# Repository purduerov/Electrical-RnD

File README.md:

# Electrical-RnD

To create a new project:
1. Before you begin work, pull recent updates from the repo with:
	
	`git switch master`
	Or if you're old fashioned `git checkout master`.

	Then: `git pull`

2. Create a new branch for your part with (replace NEW_BRANCH_NAME with your own _new_ branch name):
	Make the branch name something descriptive like (Pi-Shield-Parts or Molex-nanofit)
  
	`git checkout -b NEW_BRANCH_NAME`
  
3. Create a folder for your project
	This helps keep the repo clean, please do it
	Give the folder the same name as the branch (Not required but it makes things simpler)
	`mkdir FOLDERNAME`
	`cd FOLDERNAME`

4. Work on your project
	Keep all of your files inside the project folder
	Download the datasheet for any part you use and save it in the project folder

4. Getting rid of eagle's backup files:

	`git clean -n -X`  To see what files would be removed  
	`git clean -f -X`  To remove said files

5. Add your changes with:

	`git add .`

6. Commit your changes (this saves them) with (replace your message with an explanation of what was added):

	`git commit -m "YOUR MESSAGE"`
	ex: `git commit -m "Made the 4 pin molex 371/372 series miniclamp connector (part XXXX) for the backplane board."`

7. Push your changes to the remote repo with (use the same name as before):

	`git push`.
	If the branch was just created, do `git push -u origin NEW_BRANCH_NAME`
	
8. Open a pull request on [GitHub](https://github.com/purduerov/Electrical-RnD/pulls) to merge your branch into master.

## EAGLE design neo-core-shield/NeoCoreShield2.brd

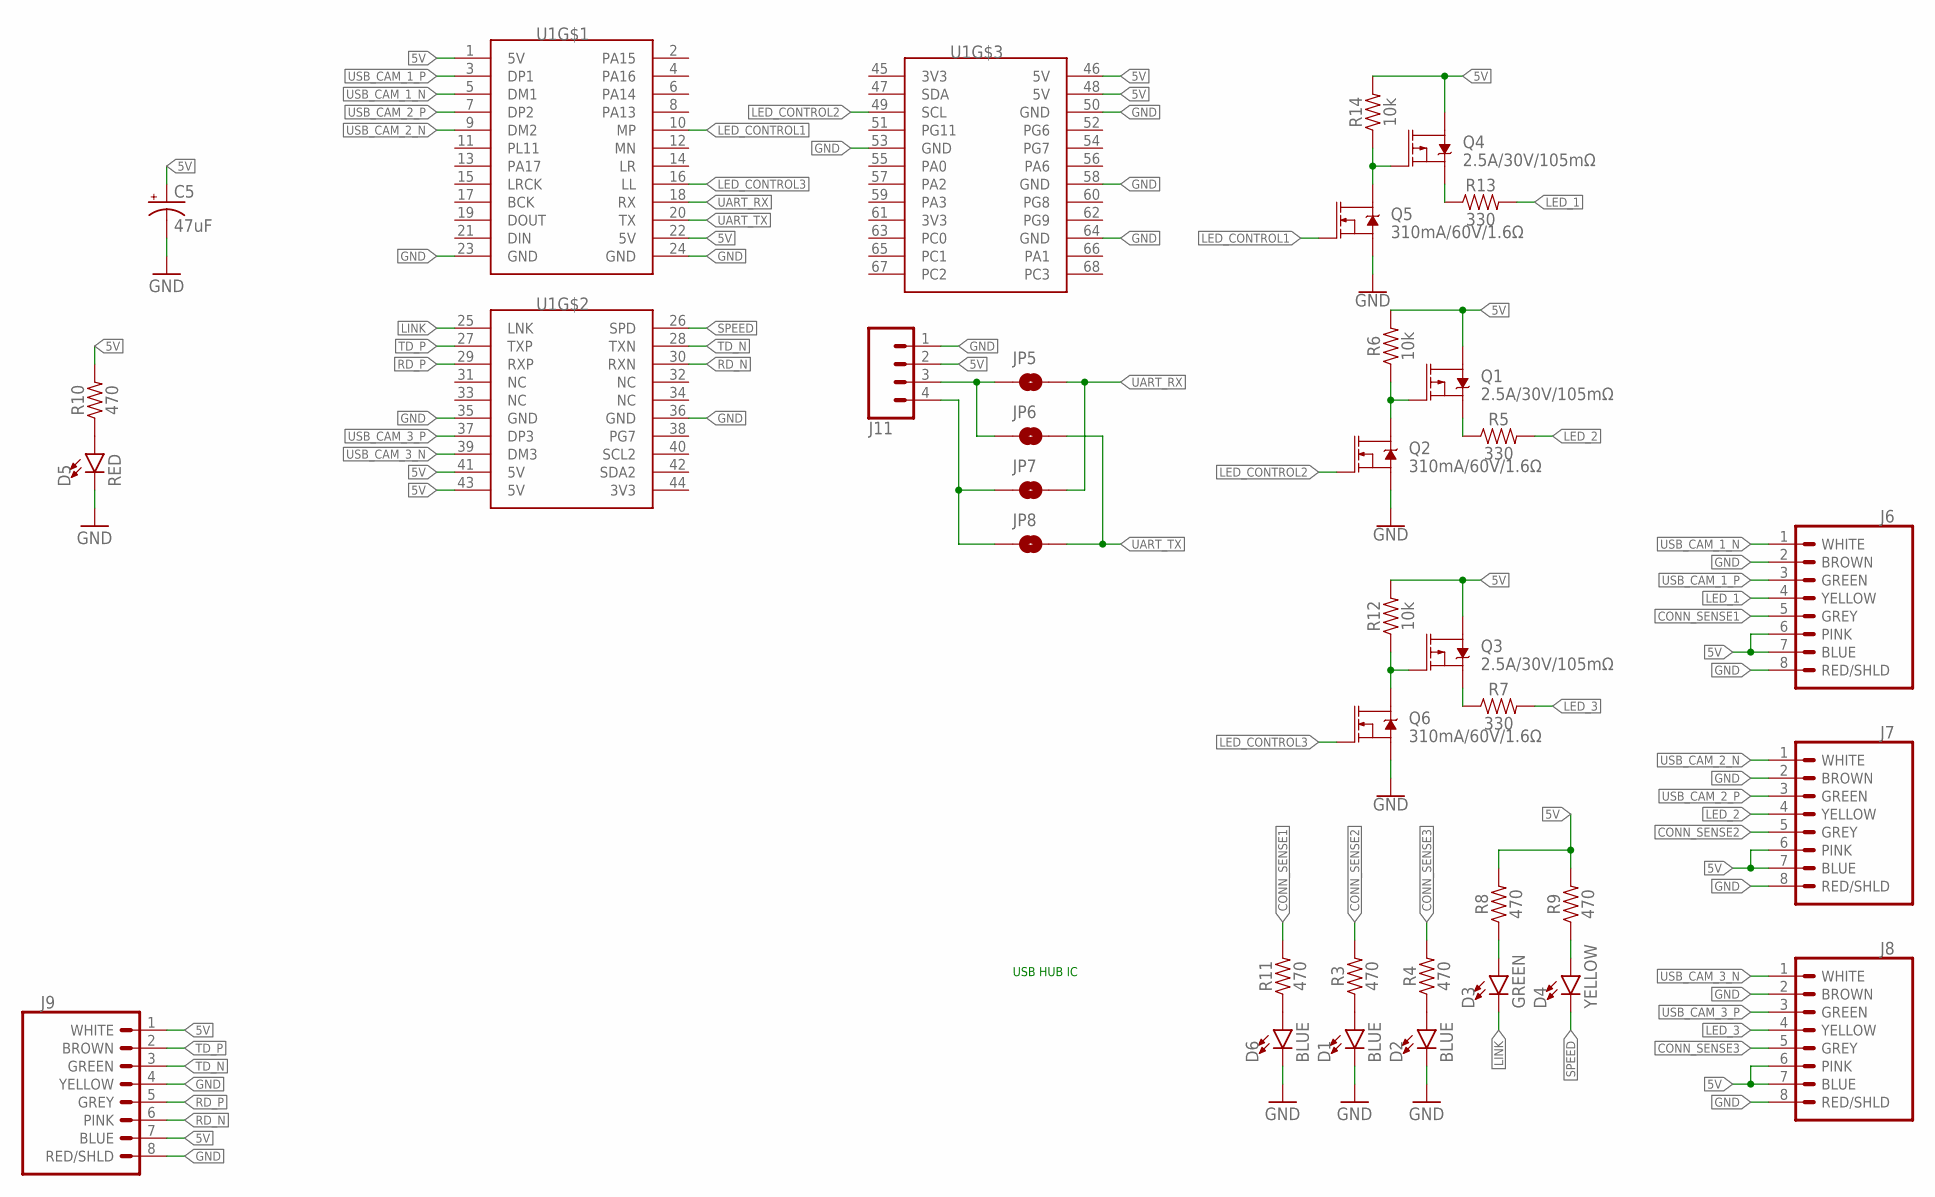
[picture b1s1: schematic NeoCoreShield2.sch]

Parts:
C5: 47uF; PANASONIC_D
D1, D2, D6: BLUE; 0805
D3: GREEN; 0805
D4: YELLOW; 0805
D5: RED; 0805
J6, J7, J8, J9: BINDER_M12_PAR_8_DIP
J11: CONN_04; 1X04
JP5, JP6, JP7, JP8: JUMPER-SMT_2_NO_SILK; SMT-JUMPER_2_NO_SILK
Q1, Q3, Q4: 2.5A/30V/105mΩ; SOT23-3
Q2, Q5, Q6: 310mA/60V/1.6Ω; SOT323
R3, R4, R8, R9, R10, R11: 470; 0603
R5, R7, R13: 330; 0805
R6, R12, R14: 10k; 0603
U1: NANO_PI_NEO_CORE

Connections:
5V: C5.+, J6.6 (PINK), J6.7 (BLUE), J7.6 (PINK), J7.7 (BLUE), J8.6 (PINK), J8.7 (BLUE), J9.1 (WHITE), J9.7 (BLUE), J11.2, Q1.3 (D), Q3.3 (D), Q4.3 (D), R6.2, R8.2, R9.2, R10.2, R12.2, R14.2, U1.1 (5V), U1.22 (5V), U1.41 (5V), U1.43 (5V), U1.46 (5V), U1.48 (5V)
CONN_SENSE1: J6.5 (GREY), R11.2
CONN_SENSE2: J7.5 (GREY), R3.2
CONN_SENSE3: J8.5 (GREY), R4.2
GND: C5.-, D1.C, D2.C, D5.C, D6.C, J6.2 (BROWN), J6.8 (RED/SHLD), J7.2 (BROWN), J7.8 (RED/SHLD), J8.2 (BROWN), J8.8 (RED/SHLD), J9.4 (YELLOW), J9.8 (RED/SHLD), J11.1, Q2.2 (S), Q5.2 (S), Q6.2 (S), U1.23 (GND), U1.24 (GND), U1.35 (GND), U1.36 (GND), U1.50 (GND), U1.53 (GND), U1.58 (GND), U1.64 (GND)
LED_1: J6.4 (YELLOW), R13.2
LED_2: J7.4 (YELLOW), R5.2
LED_3: J8.4 (YELLOW), R7.2
LED_CONTROL1: Q5.1 (G), U1.10 (MP)
LED_CONTROL2: Q2.1 (G), U1.49 (SCL)
LED_CONTROL3: Q6.1 (G), U1.16 (LL)
LINK: D3.C, U1.25 (LNK)
LINK_MID: D3.A, R8.1
unnamed: D1.A, R3.1
unnamed: D2.A, R4.1
unnamed: D6.A, R11.1
unnamed: Q3.2 (S), R7.1
unnamed: Q3.1 (G), Q6.3 (D), R12.1
unnamed: D5.A, R10.1
unnamed: Q1.2 (S), R5.1
unnamed: Q1.1 (G), Q2.3 (D), R6.1
unnamed: Q4.2 (S), R13.1
unnamed: Q4.1 (G), Q5.3 (D), R14.1
RD_N: J9.6 (PINK), U1.30 (RXN)
RD_P: J9.5 (GREY), U1.29 (RXP)
SPEED: D4.C, U1.26 (SPD)
SPEED_MID: D4.A, R9.1
TD_N: J9.3 (GREEN), U1.28 (TXN)
TD_P: J9.2 (BROWN), U1.27 (TXP)
UART_RX: JP5.2, JP7.2, U1.18 (RX)
UART_RX_TX: J11.3, JP5.1, JP6.1
UART_TX: JP6.2, JP8.2, U1.20 (TX)
UART_TX_RX: J11.4, JP7.1, JP8.1
USB_CAM_1_N: J6.1 (WHITE), U1.5 (DM1)
USB_CAM_1_P: J6.3 (GREEN), U1.3 (DP1)
USB_CAM_2_N: J7.1 (WHITE), U1.9 (DM2)
USB_CAM_2_P: J7.3 (GREEN), U1.7 (DP2)
USB_CAM_3_N: J8.1 (WHITE), U1.39 (DM3)
USB_CAM_3_P: J8.3 (GREEN), U1.37 (DP3)

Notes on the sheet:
USB HUB IC

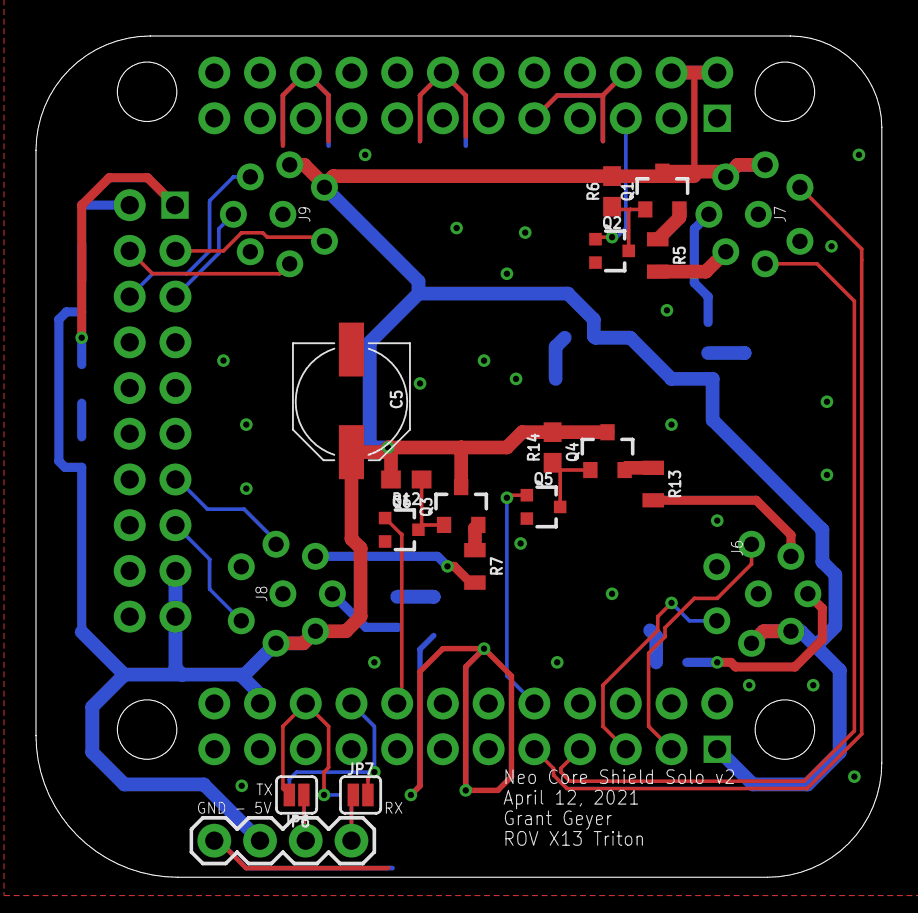
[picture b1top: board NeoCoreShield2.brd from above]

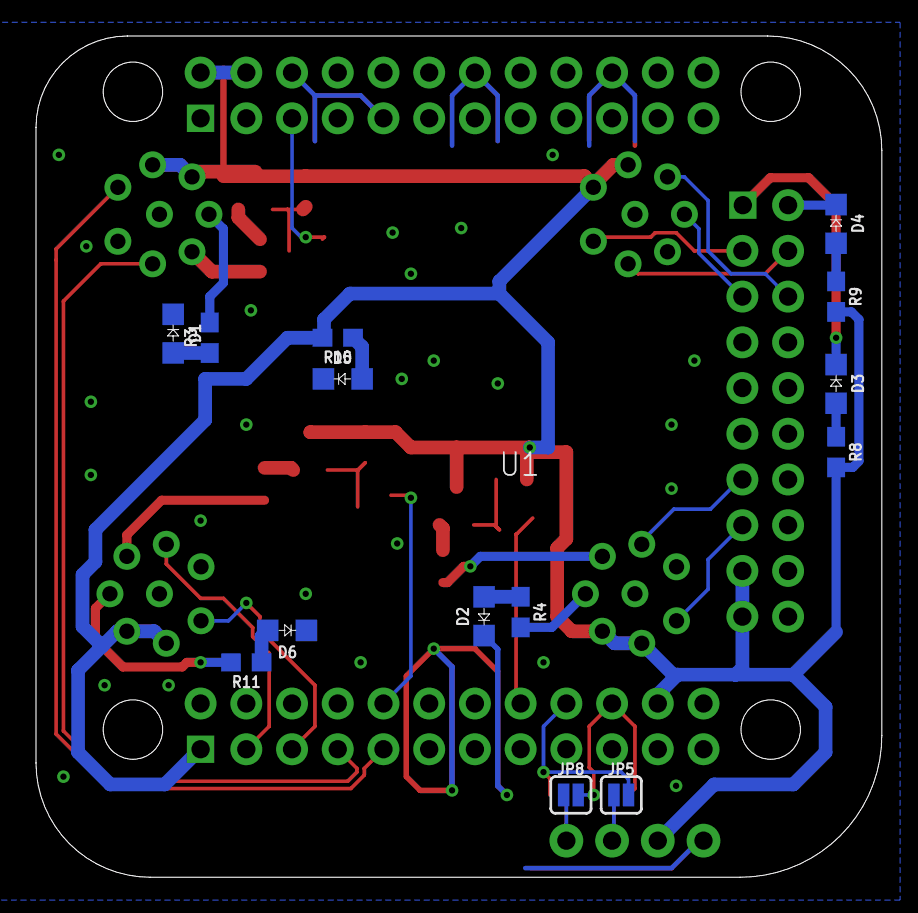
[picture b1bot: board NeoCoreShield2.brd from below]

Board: 2 copper layers, 47.0 x 46.7 mm, 35 parts (15 on the bottom side), 39 nets.

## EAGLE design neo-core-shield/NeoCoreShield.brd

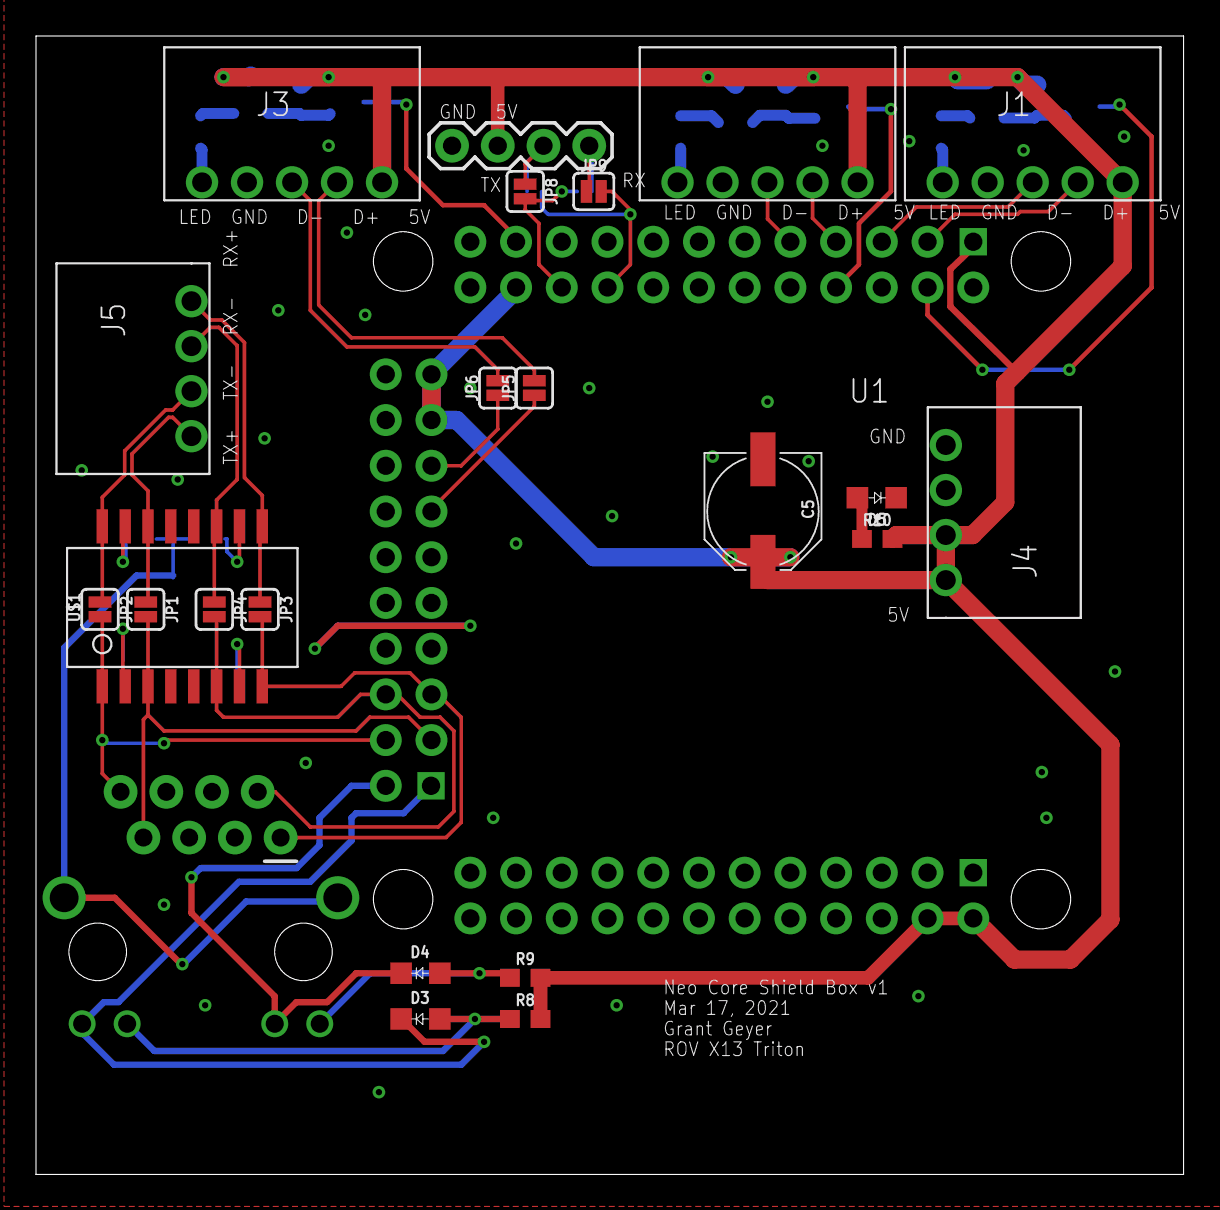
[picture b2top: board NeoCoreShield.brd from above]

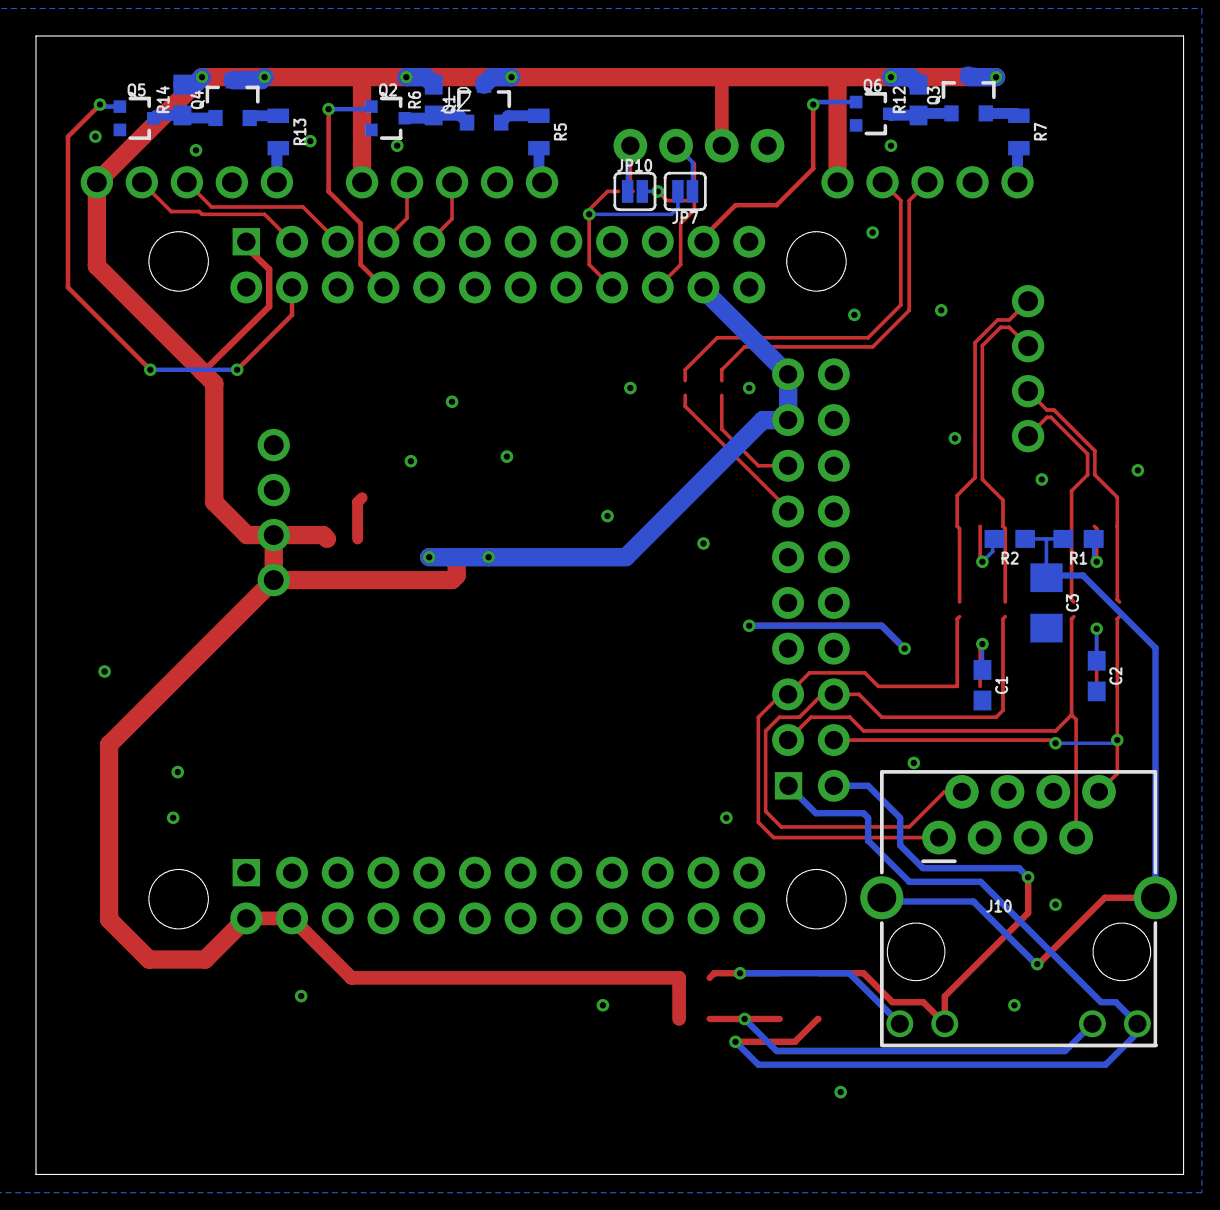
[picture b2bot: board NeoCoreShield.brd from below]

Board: 2 copper layers, 63.8 x 63.2 mm, 43 parts (20 on the bottom side), 44 nets.

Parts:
C1, C2: 0.1uF; 0603
C3: 1.0nF; 1206
C5: 47uF; PANASONIC_D
D3: GREEN; 0805
D4: YELLOW; 0805
D5: RED; 0805
J1, J2, J3: PXC-PTSM-05-RA
J4, J5: PXC-PTSM-04-RA-1778641
J10: MAGJACK
J11: 1X04
JP1, JP2, JP3, JP4, JP5, JP6, JP7, JP8, JP9, JP10: JUMPER-SMT_2_NO_SILK; SMT-JUMPER_2_NO_SILK
Q1, Q3, Q4: 2.5A/30V/105mΩ; SOT23-3
Q2, Q5, Q6: 310mA/60V/1.6Ω; SOT323
R1, R2: 75; 0603
R5, R7, R13: 330; 0805
R6, R12, R14: 10k; 0603
R8, R9, R10: 470; 0603
U1: NANO_PI_NEO_CORE
U$1: ETH-TRANS; SOIC-16-WIDE

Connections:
5V: C5.+, J1.1, J2.1, J3.1, J4.1, J4.2, J11.2, Q1.3, Q3.3, Q4.3, R6.2, R8.2, R9.2, R10.2, R12.2, R14.2, U1.1, U1.22, U1.41, U1.43, U1.46, U1.48
ETH_TD0_GND: C1.1, U$1.7
ETH_TD1_GND: C2.1, U$1.2
ETH_TERM_MID: C3.1, J10.M1, J10.M2, R1.2, R2.1
GND: C1.2, C2.2, C3.2, C5.-, D5.C, J1.4, J2.4, J3.4, J4.3, J4.4, J11.1, Q2.2, Q5.2, Q6.2, U1.23, U1.24, U1.35, U1.36, U1.50, U1.53, U1.58, U1.64
LED_1: J1.5, R13.2
LED_2: J2.5, R5.2
LED_3: J3.5, R7.2
LED_CONTROL1: Q5.1, U1.4
LED_CONTROL2: Q2.1, U1.8
LED_CONTROL3: Q6.1, U1.21
LINK: D3.C, J10.12, U1.25
LINK_MID: D3.A, J10.11, R8.1
unnamed: R2.2, U$1.10
unnamed: Q3.2, R7.1
unnamed: Q3.1, Q6.3, R12.1
unnamed: D5.A, R10.1
unnamed: Q1.2, R5.1
unnamed: Q1.1, Q2.3, R6.1
unnamed: Q4.2, R13.1
unnamed: R1.1, U$1.15
unnamed: Q4.1, Q5.3, R14.1
RD_N: J10.2, JP4.2, U1.30, U$1.6
RD_P: J10.1, JP3.2, U1.29, U$1.8
RX_N: J5.2, JP4.1, U$1.11
RX_P: J5.1, JP3.1, U$1.9
SPEED: D4.C, J10.10, U1.26
SPEED_MID: D4.A, J10.9, R9.1
TD_N: J10.8, JP2.2, U1.28, U$1.1
TD_P: J10.7, JP1.2, U1.27, U$1.3
TX_N: J5.3, JP2.1, U$1.16
TX_P: J5.4, JP1.1, U$1.14
UART_RX: JP7.2, JP9.2, U1.18
UART_RX_TX: J11.3, JP7.1, JP8.1
UART_TX: JP8.2, JP10.2, U1.20
UART_TX_RX: J11.4, JP9.1, JP10.1
USB_3_N: JP6.1, U1.39
USB_3_P: JP5.1, U1.37
USB_CAM_1_N: J1.3, U1.5
USB_CAM_1_P: J1.2, U1.3
USB_CAM_2_N: J2.3, U1.9
USB_CAM_2_P: J2.2, U1.7
USB_CAM_3_N: J3.3, JP6.2
USB_CAM_3_P: J3.2, JP5.2

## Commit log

2021-03-28 Update readme with directory bash commands
2021-03-28 Neo Core Shields
2021-03-28 Panel Jack Test boards
2021-04-05 Rectangular layout for holes
2021-04-13 Square hole pattern order
2021-04-17 Intial Commit for Compute
    why are there so many pins? ;-;
    [CHANGES: added compute device and footprint for connectors. in process of connecting pins from schematic to device. jfc there's a lot of pins wtf.]
2021-04-21 compute pi device update
    [UPDATES: renamed pads so i don't hate myself, connected symbols to footprint, device should be placeable.]
2021-04-22 Flip pinout to be correct
2021-04-30 Add schematic for the life box to power the ROV
2021-05-22 Add schematic for making a solenoid test block
2021-08-19 First version of the ESC black box code
2021-08-19 use esc class and proper constants
2021-08-19 More printing for ESC black box
2021-08-19 Telemtry and load cell versions
2021-08-22 Add schematic of current black box with notes for improvements
2021-09-02 Add node for murata 3 pin dc dc buck converter to ESC black box schematic
2021-09-02 Add missing 555 timer label
2021-10-23 Sol Board
2021-11-06 Adding a USB port placeholder, haven't made a footprint yet

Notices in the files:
parts and their libraries:
SparkFun-Resistors: Licensing: Creative Commons ShareAlike 4.0 International - https://creativecommons.org/licenses/by-sa/4.0
